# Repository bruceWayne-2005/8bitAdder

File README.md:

# 8 Bit Adder

This project demonstrates an 8-bit full adder circuit using two **IC 7483** chips. The circuit includes switches for input control and LEDs for displaying both inputs and the output sum. The result of the binary addition is shown in real-time.

## KiCad Design Files:
- **Schematic**: `8-bit adder.kicad_sch`
- **PCB Layout**: `8-bit adder.kicad_pcb`

## Getting Started:
1. Clone the repository:
    ```bash
    git clone https://github.com/bruceWayne-2005/8bitAdder.git
    ```
2. Open the KiCad project files in the KiCad application.

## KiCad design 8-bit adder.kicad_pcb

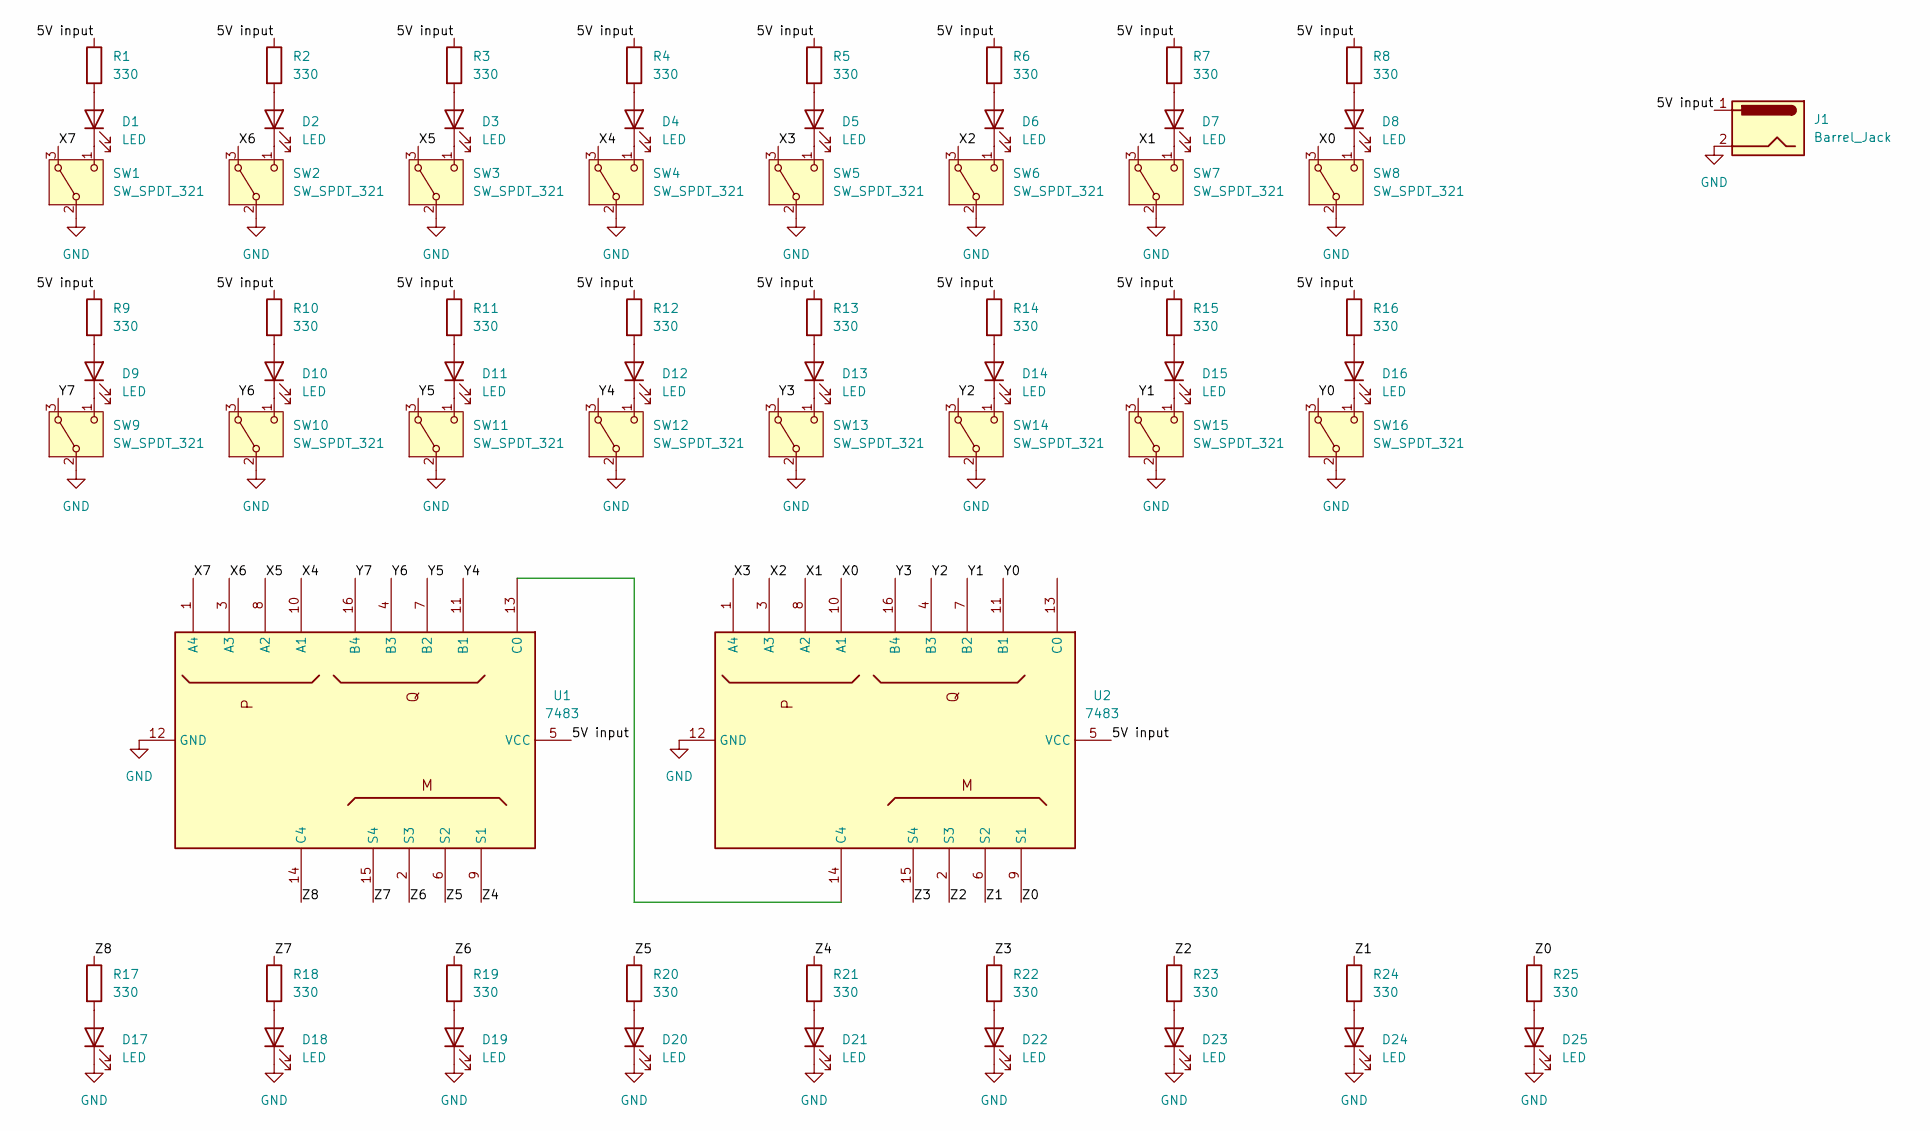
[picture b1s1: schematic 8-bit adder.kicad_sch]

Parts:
D1, D2, D3, D4, D5, D6, D7, D8, D9, D10, D11, D12, D13, D14, D15, D16, D17, D18, D19, D20, D21, D22, D23, D24, D25: LED; LED_D1.8mm_W1.8mm_H2.4mm_Horizontal_O1.27mm_Z1.6mm
J1: Barrel_Jack; Barrel_Jack_5.5mmODx2.1mmID_PJ-102A
R1, R2, R3, R4, R5, R6, R7, R8, R9, R10, R11, R12, R13, R14, R15, R16, R17, R18, R19, R20, R21, R22, R23, R24, R25: 330; R_Axial_Power_L20.0mm_W6.4mm_P5.08mm_Vertical
SW1, SW2, SW3, SW4, SW5, SW6, SW7, SW8, SW9, SW10, SW11, SW12, SW13, SW14, SW15, SW16: SW_SPDT_321; Switch_Toggle_ATE1D-2M3-10-Z
U1, U2: 7483; CERDIP-16_W7.62mm_SideBrazed_Socket

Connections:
/5V input: J1.1, R1.1, R2.1, R3.1, R4.1, R5.1, R6.1, R7.1, R8.1, R9.1, R10.1, R11.1, R12.1, R13.1, R14.1, R15.1, R16.1, U1.5 (VCC), U2.5 (VCC)
/X0: SW8.3 (A), U2.10 (A1)
/X1: SW7.3 (A), U2.8 (A2)
/X2: SW6.3 (A), U2.3 (A3)
/X3: SW5.3 (A), U2.1 (A4)
/X4: SW4.3 (A), U1.10 (A1)
/X5: SW3.3 (A), U1.8 (A2)
/X6: SW2.3 (A), U1.3 (A3)
/X7: SW1.3 (A), U1.1 (A4)
/Y0: SW16.3 (A), U2.11 (B1)
/Y1: SW15.3 (A), U2.7 (B2)
/Y2: SW14.3 (A), U2.4 (B3)
/Y3: SW13.3 (A), U2.16 (B4)
/Y4: SW12.3 (A), U1.11 (B1)
/Y5: SW11.3 (A), U1.7 (B2)
/Y6: SW10.3 (A), U1.4 (B3)
/Y7: SW9.3 (A), U1.16 (B4)
/Z0: R25.1, U2.9 (S1)
/Z1: R24.1, U2.6 (S2)
/Z2: R23.1, U2.2 (S3)
/Z3: R22.1, U2.15 (S4)
/Z4: R21.1, U1.9 (S1)
/Z5: R20.1, U1.6 (S2)
/Z6: R19.1, U1.2 (S3)
/Z7: R18.1, U1.15 (S4)
/Z8: R17.1, U1.14 (C4)
GND: D17.1 (K), D18.1 (K), D19.1 (K), D20.1 (K), D21.1 (K), D22.1 (K), D23.1 (K), D24.1 (K), D25.1 (K), J1.2, SW1.2 (B), SW2.2 (B), SW3.2 (B), SW4.2 (B), SW5.2 (B), SW6.2 (B), SW7.2 (B), SW8.2 (B), SW9.2 (B), SW10.2 (B), SW11.2 (B), SW12.2 (B), SW13.2 (B), SW14.2 (B), SW15.2 (B), SW16.2 (B), U1.12 (GND), U2.12 (GND)
unnamed: D1.2 (A), R1.2
unnamed: D1.1 (K), SW1.1 (C)
unnamed: D2.2 (A), R2.2
unnamed: D2.1 (K), SW2.1 (C)
unnamed: D3.2 (A), R3.2
unnamed: D3.1 (K), SW3.1 (C)
unnamed: D4.2 (A), R4.2
unnamed: D4.1 (K), SW4.1 (C)
unnamed: D5.2 (A), R5.2
unnamed: D5.1 (K), SW5.1 (C)
unnamed: D6.2 (A), R6.2
unnamed: D6.1 (K), SW6.1 (C)
unnamed: D7.2 (A), R7.2
unnamed: D7.1 (K), SW7.1 (C)
unnamed: D8.2 (A), R8.2
unnamed: D8.1 (K), SW8.1 (C)
unnamed: D9.2 (A), R9.2
unnamed: D9.1 (K), SW9.1 (C)
unnamed: D10.2 (A), R10.2
unnamed: D10.1 (K), SW10.1 (C)
unnamed: D11.2 (A), R11.2
unnamed: D11.1 (K), SW11.1 (C)
unnamed: D12.2 (A), R12.2
unnamed: D12.1 (K), SW12.1 (C)
unnamed: D13.2 (A), R13.2
unnamed: D13.1 (K), SW13.1 (C)
unnamed: D14.2 (A), R14.2
unnamed: D14.1 (K), SW14.1 (C)
unnamed: D15.2 (A), R15.2
unnamed: D15.1 (K), SW15.1 (C)
unnamed: D16.2 (A), R16.2
unnamed: D16.1 (K), SW16.1 (C)
unnamed: D17.2 (A), R17.2
unnamed: D18.2 (A), R18.2
unnamed: D19.2 (A), R19.2
unnamed: D20.2 (A), R20.2
unnamed: D21.2 (A), R21.2
unnamed: D22.2 (A), R22.2
unnamed: D23.2 (A), R23.2
unnamed: D24.2 (A), R24.2
unnamed: D25.2 (A), R25.2
unnamed: U1.13 (C0), U2.14 (C4)

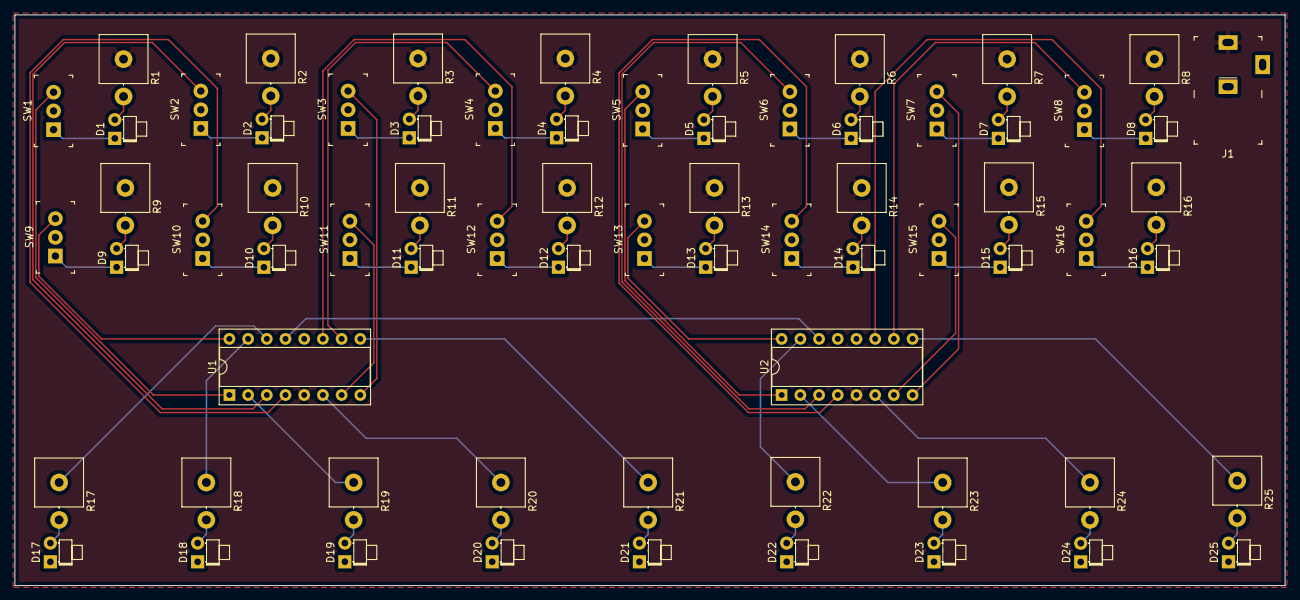
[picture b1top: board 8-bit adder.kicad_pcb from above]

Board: 2 copper layers, 172.5 x 77.5 mm, 69 parts (0 on the bottom side), 69 nets.

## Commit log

2024-12-26 added README
2024-12-26 changed README
